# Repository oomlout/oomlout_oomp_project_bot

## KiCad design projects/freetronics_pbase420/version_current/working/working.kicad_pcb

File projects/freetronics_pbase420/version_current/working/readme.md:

# PBASE420 by freetronics  
This is a harvested standardized copy of a project from github.  
The original project can be found at:  
https://github.com/freetronics/PBASE420  
Please consult that link for additional, details, files, and license information.  
Note: It was auto harvested and if the original repo had more than one board file or anything out of the ordinary the files here are likely not representative.

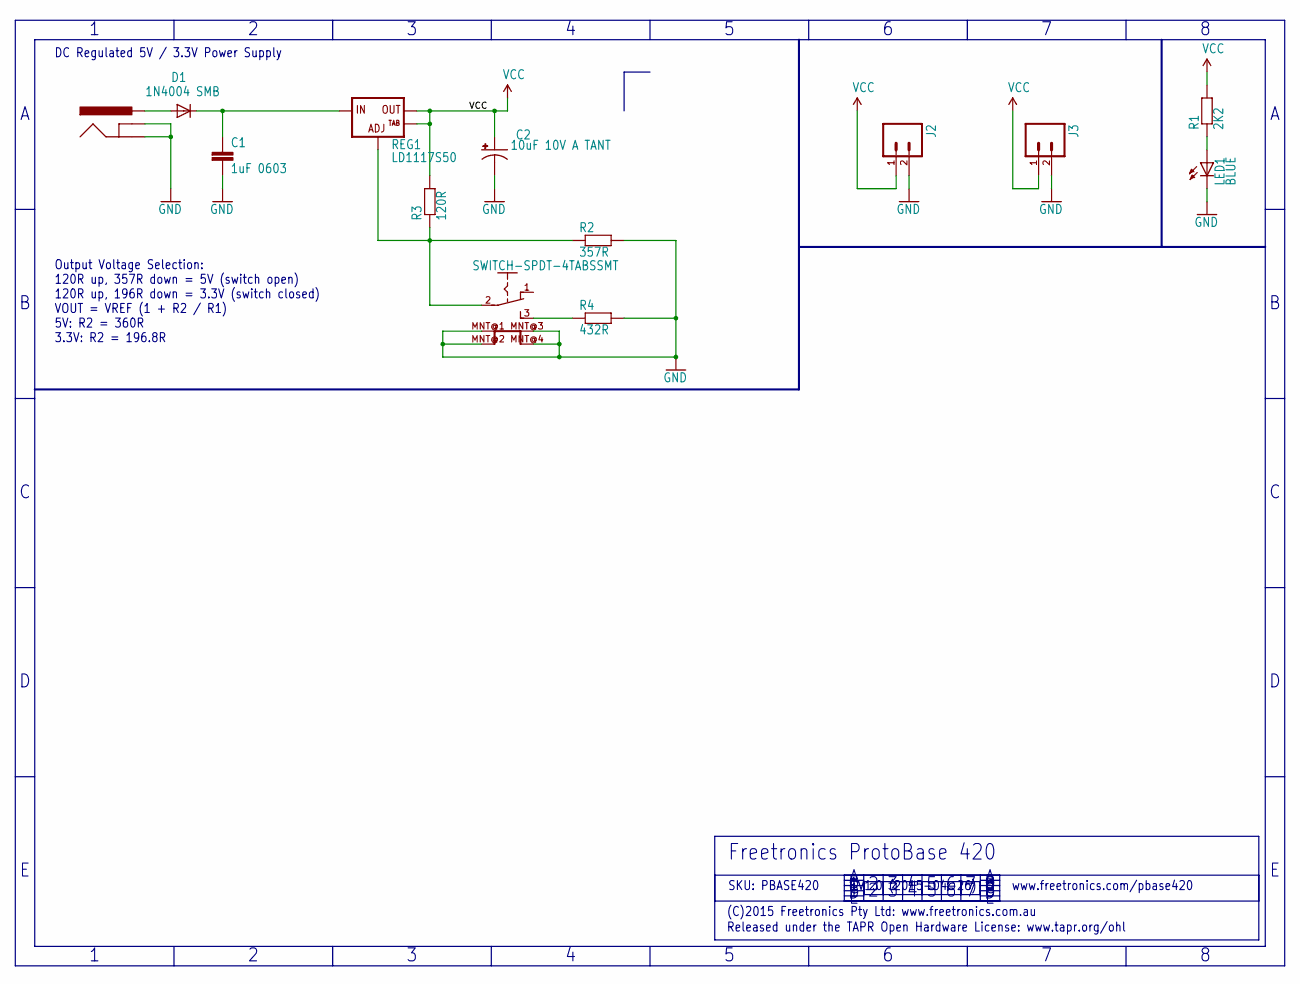
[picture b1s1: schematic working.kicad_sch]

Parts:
C1: 1uF 0603; 0603
C2: 10uF 10V A TANT; EIA3216
D1: 1N4004 SMB; SMB-DIODE
J2, J3: M02PTH; 1X02
J4: POWER_JACKPTH_SLOTS; POWER_JACK_PTH_SLOTS
LED1: BLUE; LED-0603
R1: 2K2; 0603
R2: 357R; 0603
R3: 120R; 0603
R4: 432R; 0603
REG1: LD1117S50; SOT223
SW1: SWITCH-SPDT-4TABSSMT; MK-12C02

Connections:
GND: C1.2, C2.C (-), J2.2, J3.2, J4.GND, J4.GNDBREAK, LED1.C, R2.2, R4.2, SW1.MNT@1, SW1.MNT@2, SW1.MNT@3, SW1.MNT@4
unnamed: LED1.A, R1.1
unnamed: R2.1, R3.1, REG1.1 (ADJ), SW1.2 (COM)
unnamed: R4.1, SW1.3 (B)
unnamed: D1.A, J4.PWR
VCC: C2.A (+), J2.1, J3.1, R1.2, R3.2, REG1.2 (OUT), REG1.4 (OUT@1)
VIN: C1.1, D1.C, REG1.3 (IN)

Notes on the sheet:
SKU: PBASE420
Output Voltage Selection: 120R up, 357R down = 5V (switch open) 120R up, 196R down = 3.3V (switch closed) VOUT = VREF (1 + R2 / R1) 5V: R2 = 360R 3.3V: R2 = 196.8R
www.freetronics.com/pbase420
Released under the TAPR Open Hardware License: www.tapr.org/ohl
DC Regulated 5V / 3.3V Power Supply
(C)2015 Freetronics Pty Ltd: www.freetronics.com.au
V1.0 (2015-04-26)
Freetronics ProtoBase 420

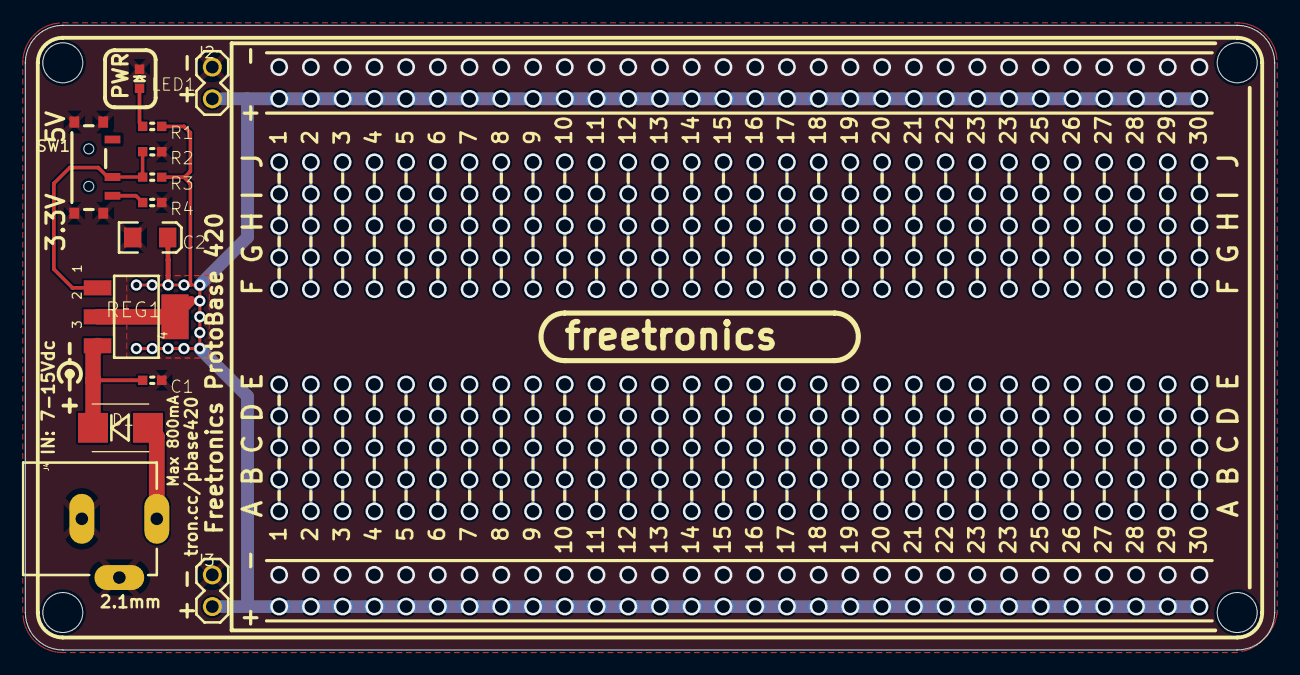
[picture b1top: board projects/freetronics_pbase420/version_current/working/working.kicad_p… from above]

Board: 2 copper layers, 100.0 x 50.0 mm, 17 parts (0 on the bottom side), 7 nets.

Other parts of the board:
@HOLE0, @HOLE1, @HOLE2, @HOLE3: (no value)

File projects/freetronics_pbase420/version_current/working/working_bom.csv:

"Id";"Designator";"Footprint";"Quantity";"Designation";"Supplier and ref";
1;"@HOLE3,@HOLE0,@HOLE2,@HOLE1";"";4;"";;;
2;"J2,J3";"1X02";2;"";;;
3;"R1";"0603";1;"2K2";;;
4;"R2";"0603";1;"357R";;;
5;"SW1";"MK-12C02";1;"MK-12C02-PB";;;
6;"R3";"0603";1;"120R";;;
7;"LED1";"LED-0603";1;"BLUE";;;
8;"D1";"SMB-DIODE";1;"1N4004 SMB";;;
9;"R4";"0603";1;"432R";;;
10;"REG1";"SOT223";1;"LD1117S50";;;
11;"C2";"EIA3216";1;"10uF 10V A TANT";;;
12;"C1";"0603";1;"1uF 0603";;;
13;"J4";"POWER_JACK_PTH_SLOTS";1;"POWER_JACKPTH_SLOTS";;;

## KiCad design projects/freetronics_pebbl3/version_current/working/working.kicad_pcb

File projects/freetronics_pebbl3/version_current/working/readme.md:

# PEBBL3 by freetronics  
This is a harvested standardized copy of a project from github.  
The original project can be found at:  
https://github.com/freetronics/PEBBL3  
Please consult that link for additional, details, files, and license information.  
Note: It was auto harvested and if the original repo had more than one board file or anything out of the ordinary the files here are likely not representative.

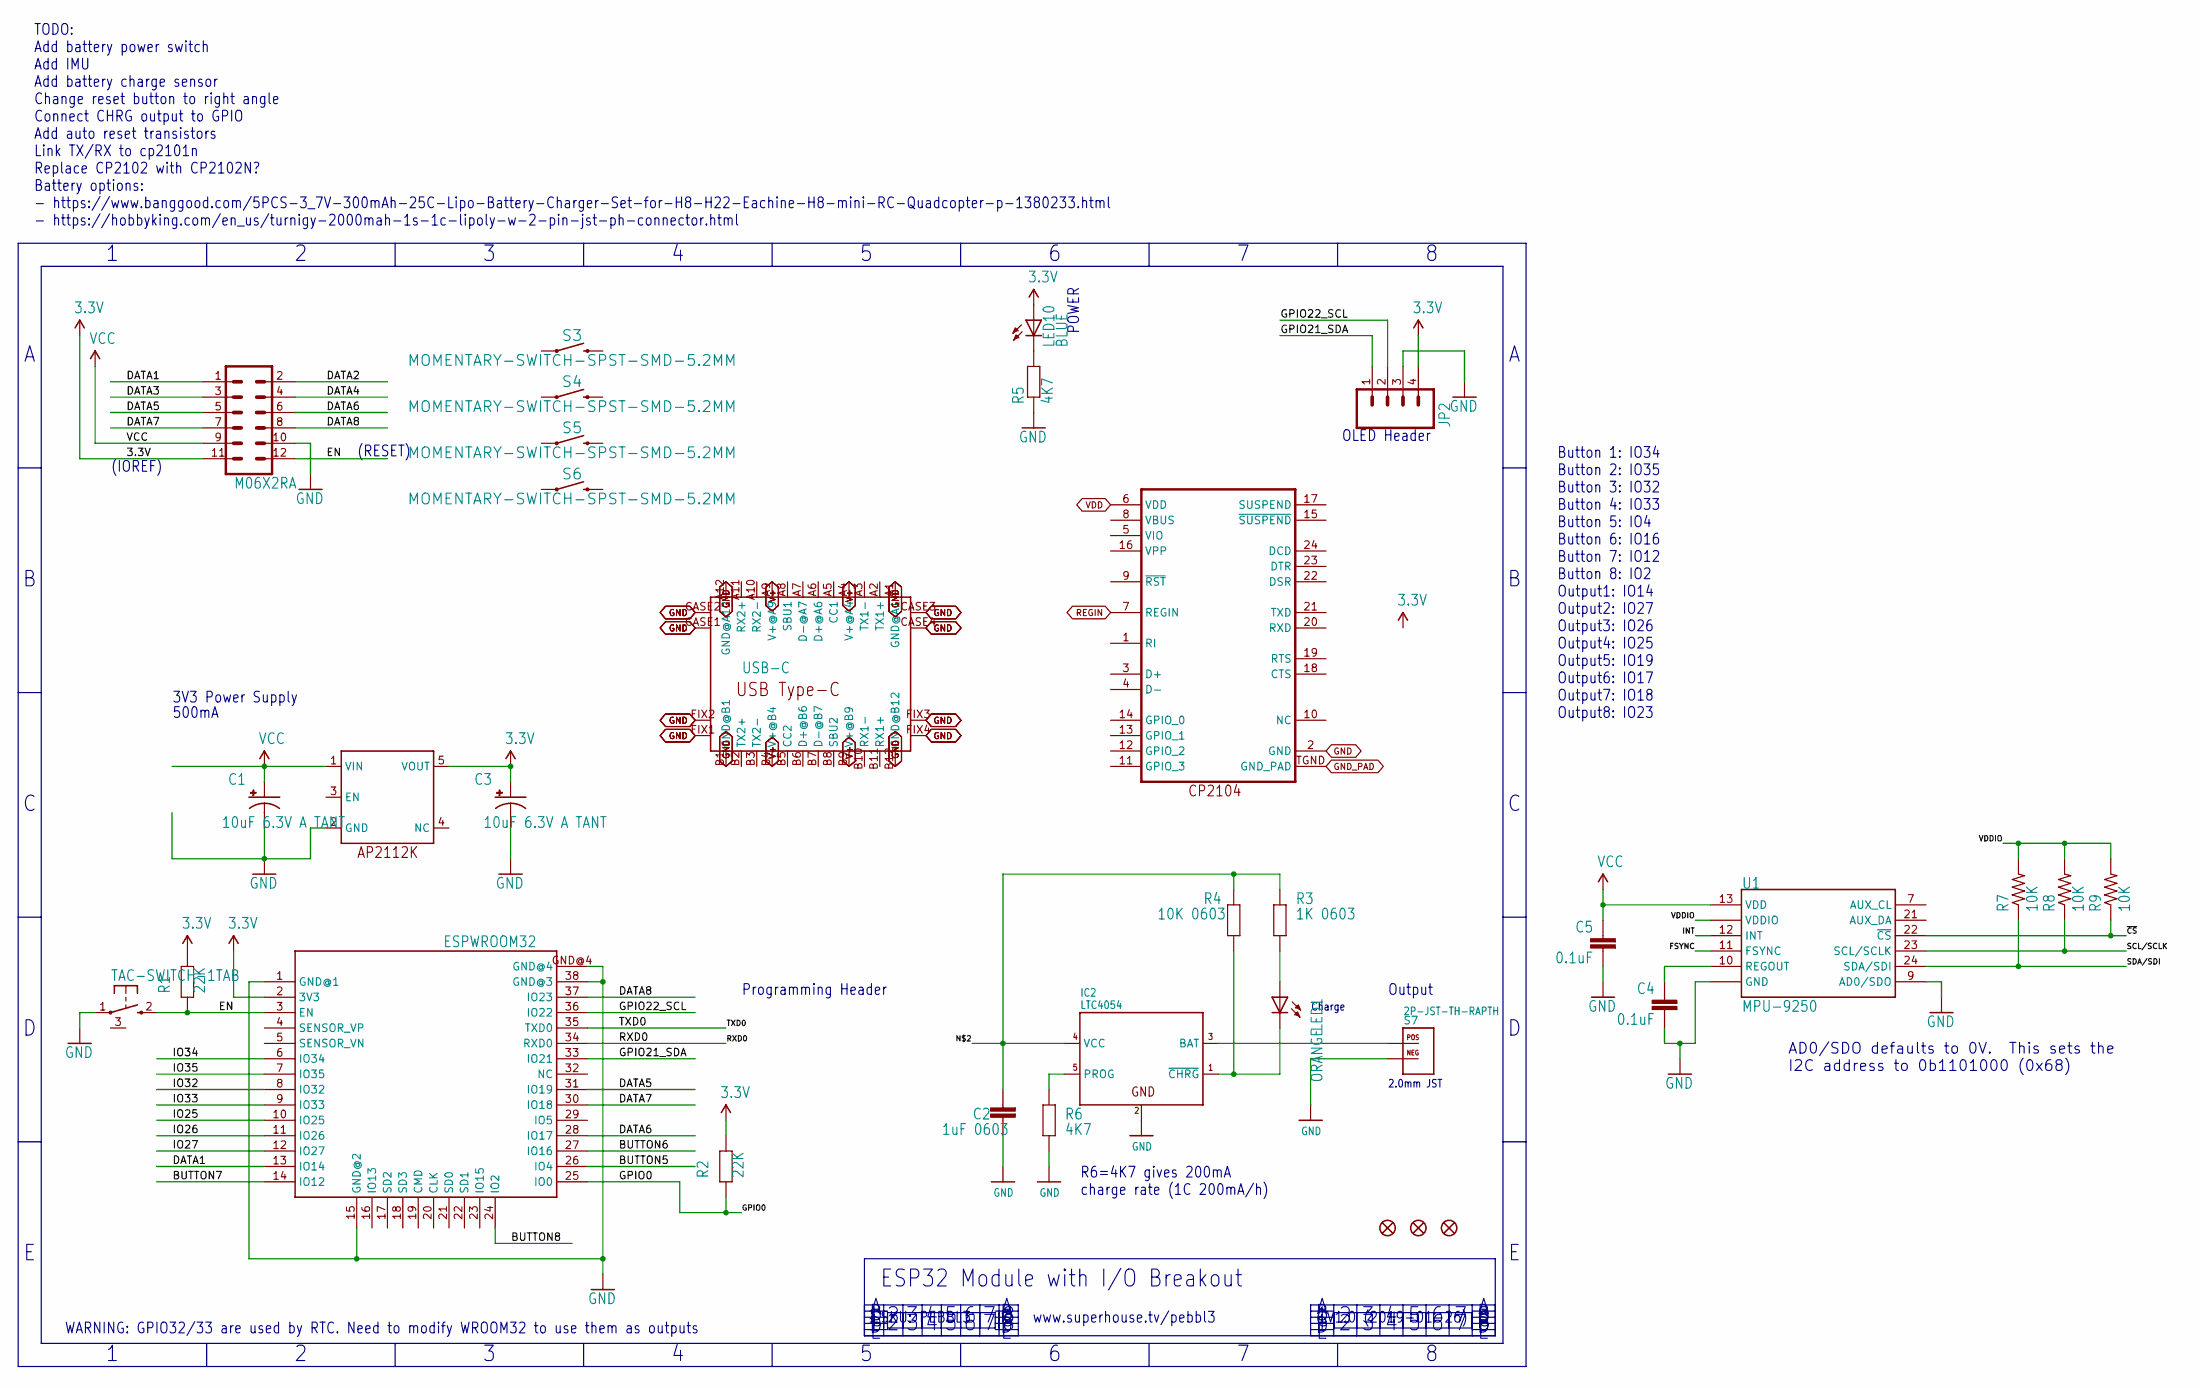
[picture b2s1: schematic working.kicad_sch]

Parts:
C1, C3: 10uF 6.3V A TANT; EIA3216
C2: 1uF 0603; 0603
C4, C5: 0.1uF; 0603-CAP
FID1, FID2, FID3: FIDUCIAL1X2.5; FIDUCIAL-1X2.5
IC1: ESPWROOM32
IC2: LTC4054; SOT23-5
JP2: M04PTH; 1X04
LED1: ORANGE; LED-0603
LED10: BLUE; LED-0603
R1, R2: 22K; 0603
R3: 1K 0603; 0603
R4: 10K 0603; 0603
R5, R6: 4K7; 0603
R7, R8, R9: 10K; 0603-RES
S1: TAC-SWITCH-1TAB; TACT-VERT-1TAB
S3, S4, S5, S6: MOMENTARY-SWITCH-SPST-SMD-5.2MM; TACTILE_SWITCH_SMD_5.2MM
S7: 2P-JST-TH-RAPTH; JST-2MM-TH-RA
U1: MPU-9250; QFN24_PAD
U$1: USB-C; USB-C-U52A
U$2: AP2112KSOT25; SOT23-5
U$3: CP2104; QFN-24
U$6: M06X2RA; 2X6-SHROUDED-RA

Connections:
3.3V: C3.A (+), IC1.2 (3V3), JP2.4, LED10.A, R1.1, R2.1, U$2.5 (VOUT), U$6.11
BUTTON5: IC1.26 (IO4)
BUTTON6: IC1.27 (IO16)
BUTTON7: IC1.14 (IO12)
BUTTON8: IC1.24 (IO2)
DATA1: IC1.13 (IO14), U$6.1
DATA2: U$6.2
DATA3: U$6.3
DATA4: U$6.4
DATA5: IC1.31 (IO19), U$6.5
DATA6: IC1.28 (IO17), U$6.6
DATA7: IC1.30 (IO18), U$6.7
DATA8: IC1.37 (IO23), U$6.8
EN: IC1.3 (EN), R1.2, S1.2, U$6.12
FSYNC: U1.11 (FSYNC)
GND: C1.C (-), C2.1, C3.C (-), C4.2, C5.2, IC1.1 (GND@1), IC1.15 (GND@2), IC1.38 (GND@3), IC1.GND@4, IC2.2 (GND), JP2.3, R5.1, R6.2, S1.1, S7.NEG, U1.9 (AD0/SDO), U1.18 (GND), U1.20 (GND), U1.CENTER (GND), U$1.A1 (GND@A1), U$1.A12 (GND@A12), U$1.B1 (GND@B1), U$1.B12 (GND@B12), U$1.CASE1 (GND@CASE1), U$1.CASE2 (GND@CASE2), U$1.CASE3 (GND@CASE3), U$1.CASE4 (GND@CASE4), U$1.FIX1 (GND@FIX1), U$1.FIX2 (GND@FIX2), U$1.FIX3 (GND@FIX3), U$1.FIX4 (GND@FIX4), U$2.2 (GND), U$3.2 (GND), U$6.10
GND_PAD: U$3.TGND (GND_PAD)
GPIO0: IC1.25 (IO0), R2.2
GPIO21_SDA: IC1.33 (IO21), JP2.1
GPIO22_SCL: IC1.36 (IO22), JP2.2
INT: U1.12 (INT)
IO25: IC1.10 (IO25)
IO26: IC1.11 (IO26)
IO27: IC1.12 (IO27)
IO32: IC1.8 (IO32)
IO33: IC1.9 (IO33)
IO34: IC1.6 (IO34)
IO35: IC1.7 (IO35)
unnamed: C2.2, IC2.4 (VCC), R3.1, R4.1
unnamed: IC2.5 (PROG), R6.1
unnamed: IC2.3 (BAT), S7.POS
unnamed: IC2.1 (~CHRG), LED1.C, R4.2
unnamed: LED1.A, R3.2
unnamed: LED10.C, R5.2
REGIN: U$3.7 (REGIN)
REGOUT: C4.1, U1.10 (REGOUT)
RXD0: IC1.34 (RXD0)
SCL/SCLK: R8.1, U1.23 (SCL/SCLK)
SDA/SDI: R7.1, U1.24 (SDA/SDI)
TXD0: IC1.35 (TXD0)
V+: U$1.A4 (V+@A4), U$1.A9 (V+@A9), U$1.B4 (V+@B4), U$1.B9 (V+@B9)
VDDIO: R7.2, R8.2, R9.2, U1.1 (VDDIO), U1.8 (VDDIO)
~CS: R9.1, U1.22 (~CS)

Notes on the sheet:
Charge
(RESET)
OLED Header
AD0/SDO defaults to 0V. This sets the I2C address to 0b1101000 (0x68)
Output
POWER
2.0mm JST
WARNING: GPIO32/33 are used by RTC. Need to modify WROOM32 to use them as outputs
(IOREF)
Button 1: IO34 Button 2: IO35 Button 3: IO32 Button 4: IO33 Button 5: IO4 Button 6: IO16 Button 7: IO12 Button 8: IO2 Output1: IO14 Output2: IO27 Output3: IO26 Output4: IO25 Output5: IO19 Output6: IO17 Output7: IO18 Output8: IO23
3V3 Power Supply
TODO: Add battery power switch Add IMU Add battery charge sensor Change reset button to right angle Connect CHRG output to GPIO Add auto reset transistors Link TX/RX to cp2101n Replace CP2102 with CP2102N? Battery options: - https://www.banggood.com/5PCS-3_7V-300mAh-25C-Lipo-Battery-Charger-Set-for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
ESP32 Module with I/O Breakout
SKU: PEBBL3
R6=4K7 gives 200mA charge rate (1C 200mA/h)
500mA
V1.0 (2019-01-26)
www.superhouse.tv/pebbl3
Programming Header

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
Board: 2 copper layers, 33 parts (5 on the bottom side), 25 nets, no tracks yet.

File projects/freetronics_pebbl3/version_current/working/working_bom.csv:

"Id";"Designator";"Footprint";"Quantity";"Designation";"Supplier and ref";
1;"S6,S3,S5,S4";"TACTILE_SWITCH_SMD_5.2MM";4;"MOMENTARY-SWITCH-SPST-SMD-5.2MM";;;
2;"R5,R6";"0603";2;"4K7";;;
3;"R1,R2";"0603";2;"22K";;;
4;"R9,R7,R8";"0603-RES";3;"10K";;;
5;"LED10";"LED-0603";1;"BLUE";;;
6;"C4,C5";"0603-CAP";2;"0.1uF";;;
7;"U$3";"QFN-24";1;"CP2104";;;
8;"C3,C1";"EIA3216";2;"10uF 6.3V A TANT";;;
9;"FID3,FID1,FID2";"FIDUCIAL-1X2.5";3;"FIDUCIAL1X2.5";;;
10;"U$2";"SOT23-5";1;"AP2112KSOT25";;;
11;"R3";"0603";1;"1K 0603";;;
12;"U1";"QFN24_PAD";1;"MPU-9250";;;
13;"R4";"0603";1;"10K 0603";;;
14;"LED1";"LED-0603";1;"ORANGE";;;
15;"C2";"0603";1;"1uF 0603";;;
16;"IC2";"SOT23-5";1;"LTC4054";;;
17;"JP2";"1X04";1;"";;;
18;"U$1";"USB-C-U52A";1;"USB-C";;;
19;"S7";"JST-2MM-TH-RA";1;"2P-JST-PTH";;;
20;"S1";"TACT-VERT-1TAB";1;"RESET";;;
21;"U$6";"2X6-SHROUDED-RA";1;"M06X2RA";;;
22;"IC1";"ESPWROOM32";1;"ESPWROOM32";;;

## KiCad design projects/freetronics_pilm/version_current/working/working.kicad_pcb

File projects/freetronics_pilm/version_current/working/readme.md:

# PILM by freetronics  
This is a harvested standardized copy of a project from github.  
The original project can be found at:  
https://github.com/freetronics/PILM  
Please consult that link for additional, details, files, and license information.  
Note: It was auto harvested and if the original repo had more than one board file or anything out of the ordinary the files here are likely not representative.

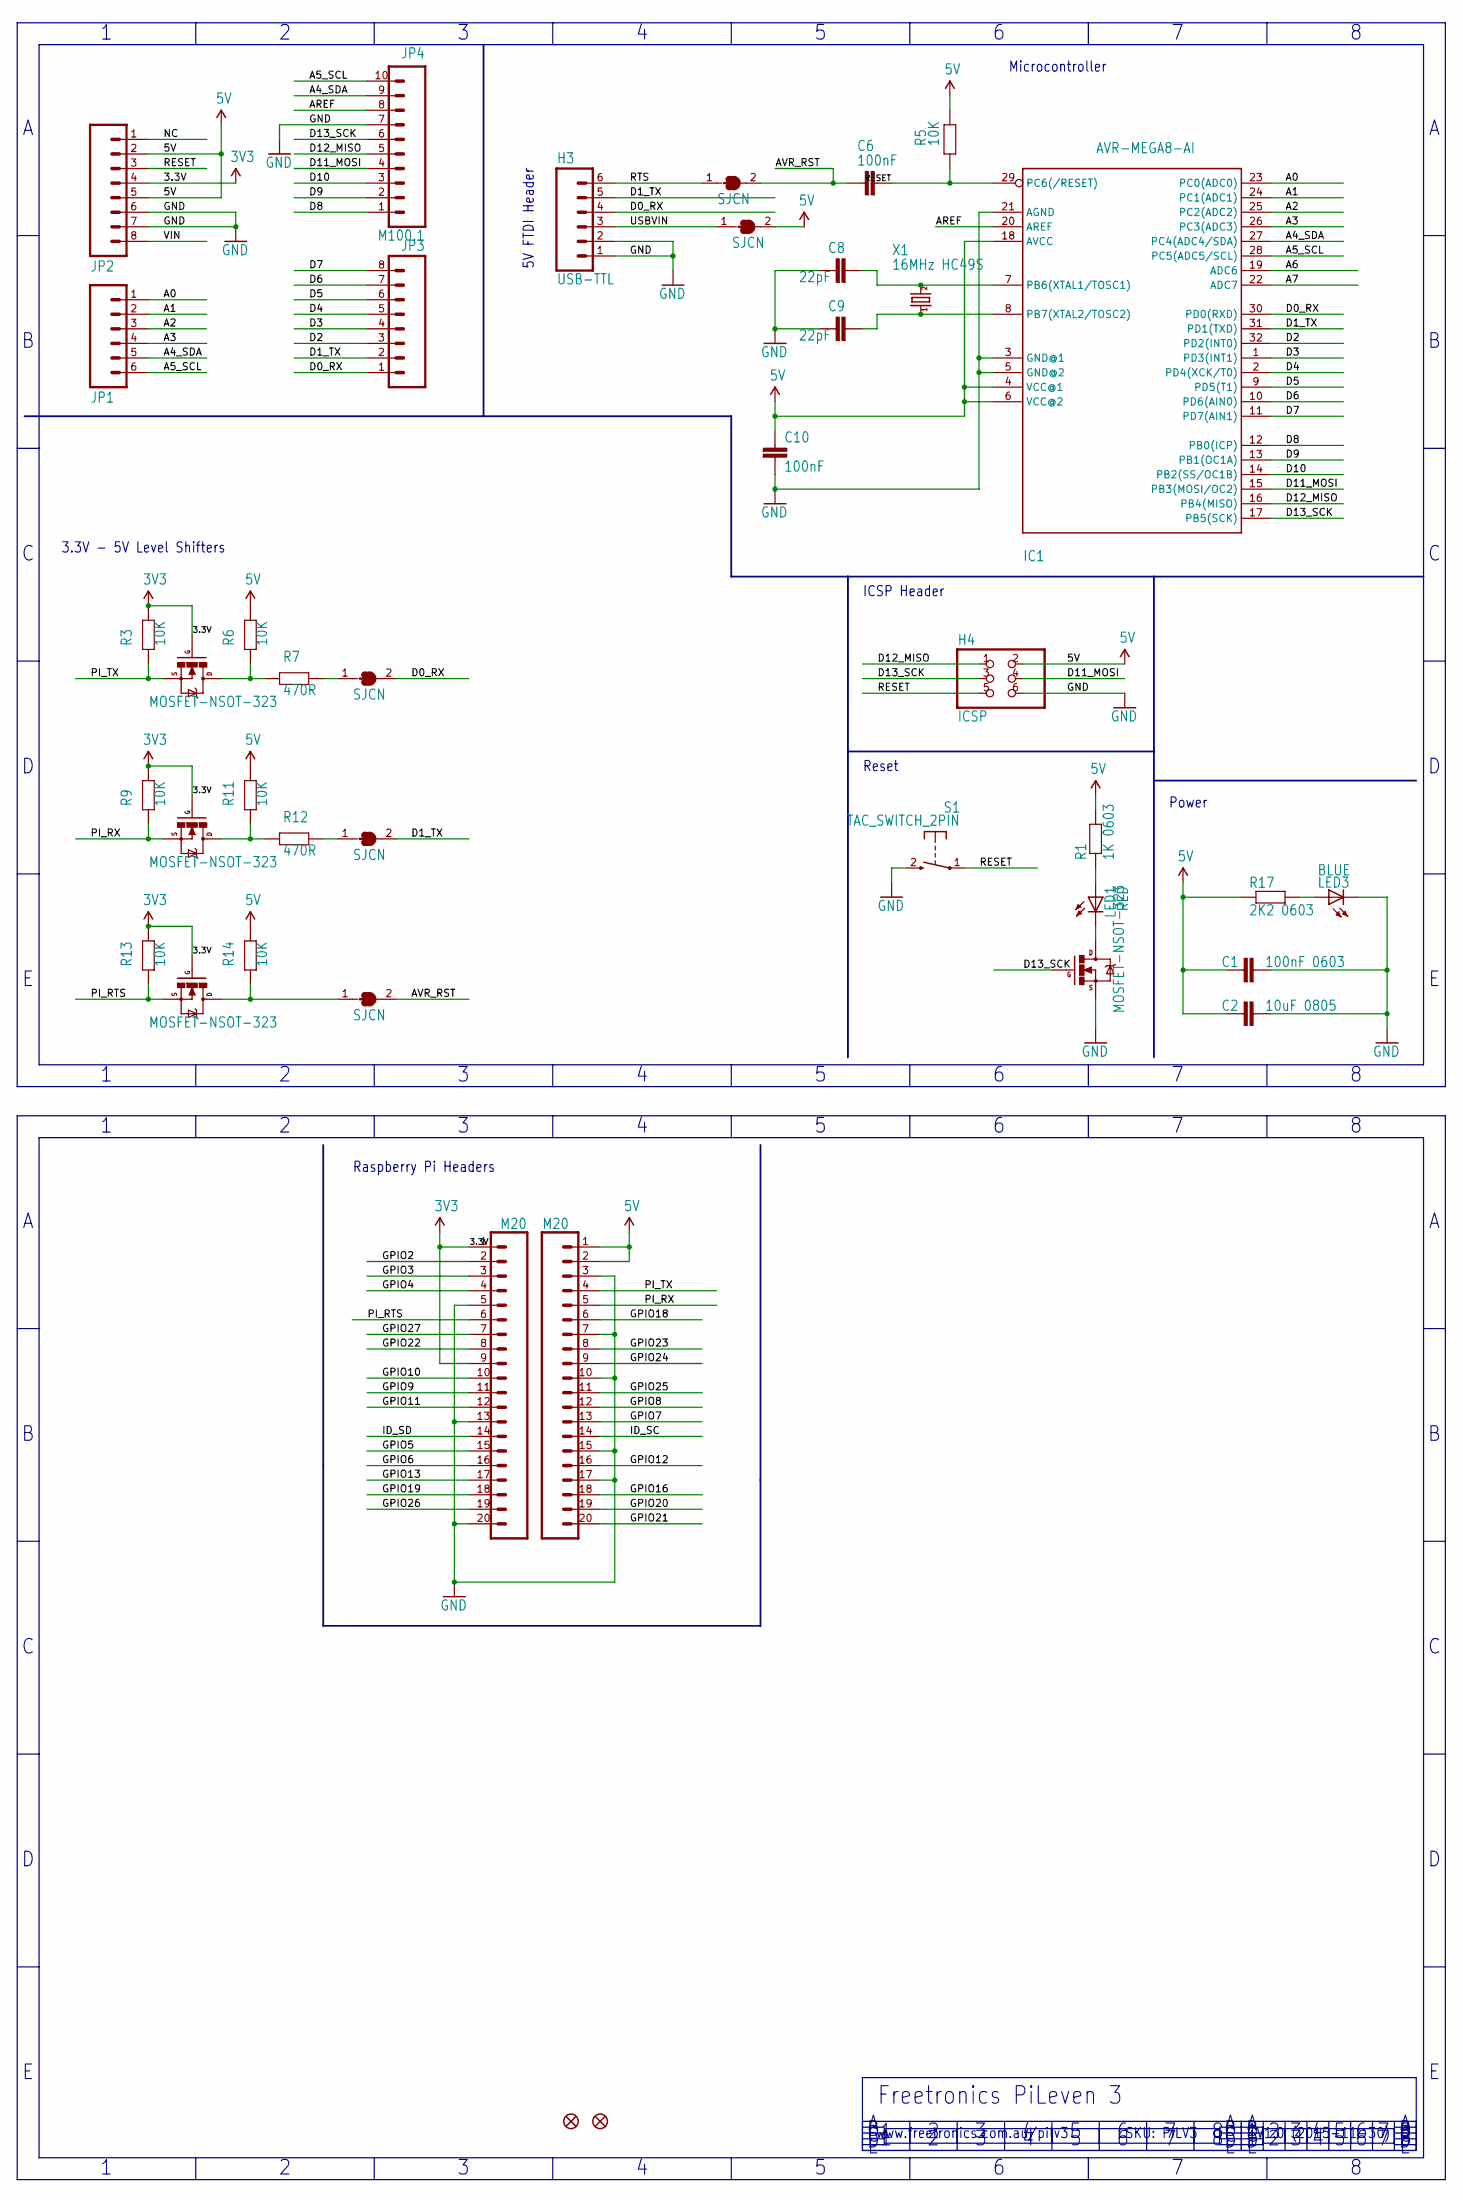
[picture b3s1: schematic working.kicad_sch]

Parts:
C1: 100nF 0603; 0603
C2: 10uF 0805; C0805
C6, C10: 100nF; 0603
C8, C9: 22pF; 0603
H1, H2: M20; 1X20
H3: USB-TTL; 1X06
H4: ICSP; 2X03
IC1: AVR-MEGA8-AI; TQFP32-08
JP1: M06SIP; 1X06
JP2, JP3: M08; 1X08
JP4: M100.1; 1X10
LED1: RED; LED-0603
LED3: BLUE; LED-0603
Q1, Q2, Q3, Q4: MOSFET-NSOT-323; SOT32-3
R1: 1K 0603; 0603
R3, R5, R6, R9, R11, R13, R14: 10K; 0603
R7, R12: 470R; 0603
R17: 2K2 0603; 0603
S1: TAC_SWITCH_2PIN; TACTILE_SWITCH_SMD_2PIN_TINY
SJ1, SJ2, SJ3, SJ4, SJ5: SJCN; SJC
U$4, U$5: FIDUCIAL1X2.5; FIDUCIAL-1X2.5
X1: 16MHz HC49S; HC49U-V

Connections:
3.3V: H1.1, H1.9, JP2.4, Q1.1 (G), Q2.1 (G), Q3.1 (G), R3.1, R9.1, R13.1
5V: C1.1, C2.2, C10.1, H2.1, H2.2, H4.2, IC1.4 (VCC@1), IC1.6 (VCC@2), IC1.18 (AVCC), JP2.2, JP2.5, R1.2, R5.2, R6.1, R11.1, R14.1, R17.1, SJ2.2
A0: IC1.23 (PC0(ADC0)), JP1.1
A1: IC1.24 (PC1(ADC1)), JP1.2
A2: IC1.25 (PC2(ADC2)), JP1.3
A3: IC1.26 (PC3(ADC3)), JP1.4
A4_SDA: IC1.27 (PC4(ADC4/SDA)), JP1.5, JP4.9
A5_SCL: IC1.28 (PC5(ADC5/SCL)), JP1.6, JP4.10
A6: IC1.19 (ADC6)
A7: IC1.22 (ADC7)
AREF: IC1.20 (AREF), JP4.8
AVR_RST: C6.1, SJ1.2, SJ5.2
D0_RX: H3.4, IC1.30 (PD0(RXD)), JP3.1, SJ3.2
D1_TX: H3.5, IC1.31 (PD1(TXD)), JP3.2, SJ4.2
D2: IC1.32 (PD2(INT0)), JP3.3
D3: IC1.1 (PD3(INT1)), JP3.4
D4: IC1.2 (PD4(XCK/T0)), JP3.5
D5: IC1.9 (PD5(T1)), JP3.6
D6: IC1.10 (PD6(AIN0)), JP3.7
D7: IC1.11 (PD7(AIN1)), JP3.8
D8: IC1.12 (PB0(ICP)), JP4.1
D9: IC1.13 (PB1(OC1A)), JP4.2
D10: IC1.14 (PB2(SS/OC1B)), JP4.3
D11_MOSI: H4.4, IC1.15 (PB3(MOSI/OC2)), JP4.4
D12_MISO: H4.1, IC1.16 (PB4(MISO)), JP4.5
D13_SCK: H4.3, IC1.17 (PB5(SCK)), JP4.6, Q4.1 (G)
GND: C1.2, C2.1, C8.1, C9.1, C10.2, H1.5, H1.13, H1.20, H2.3, H2.7, H2.10, H2.15, H2.17, H3.1, H3.2, H4.6, IC1.3 (GND@1), IC1.5 (GND@2), IC1.21 (AGND), JP2.6, JP2.7, JP4.7, LED3.C, Q4.2 (S), S1.2 (S)
GPIO2: H1.2
GPIO3: H1.3
GPIO4: H1.4
GPIO5: H1.15
GPIO6: H1.16
GPIO7: H2.13
GPIO8: H2.12
GPIO9: H1.11
GPIO10: H1.10
GPIO11: H1.12
GPIO12: H2.16
GPIO13: H1.17
GPIO16: H2.18
GPIO18: H2.6
GPIO19: H1.18
GPIO20: H2.19
GPIO21: H2.20
GPIO22: H1.8
GPIO23: H2.8
GPIO24: H2.9
GPIO25: H2.11
GPIO26: H1.19
GPIO27: H1.7
ID_SC: H2.14
ID_SD: H1.14
unnamed: LED3.A, R17.2
unnamed: Q1.3 (D), R6.2, R7.2
unnamed: R7.1, SJ3.1
unnamed: R12.1, SJ4.1
unnamed: C8.2, IC1.7 (PB6(XTAL1/TOSC1)), X1.2
unnamed: Q2.3 (D), R11.2, R12.2
unnamed: Q3.3 (D), R14.2, SJ5.1
unnamed: LED1.C, Q4.3 (D)
unnamed: LED1.A, R1.1
unnamed: C9.2, IC1.8 (PB7(XTAL2/TOSC2)), X1.1
NC: JP2.1
PI_RTS: H1.6, Q3.2 (S), R13.2
PI_RX: H2.5, Q2.2 (S), R9.2
PI_TX: H2.4, Q1.2 (S), R3.2
RESET: C6.2, H4.5, IC1.29 (PC6(/RESET)), JP2.3, R5.1, S1.1
RTS: H3.6, SJ1.1
USBVIN: H3.3, SJ2.1
VIN: JP2.8

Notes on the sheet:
Microcontroller
Freetronics PiLeven 3
Power
www.freetronics.com.au/pilv3
3.3V - 5V Level Shifters
ICSP Header
SKU: PILV3
5V FTDI Header
V1.0 (2015-11-30)
Reset
Raspberry Pi Headers

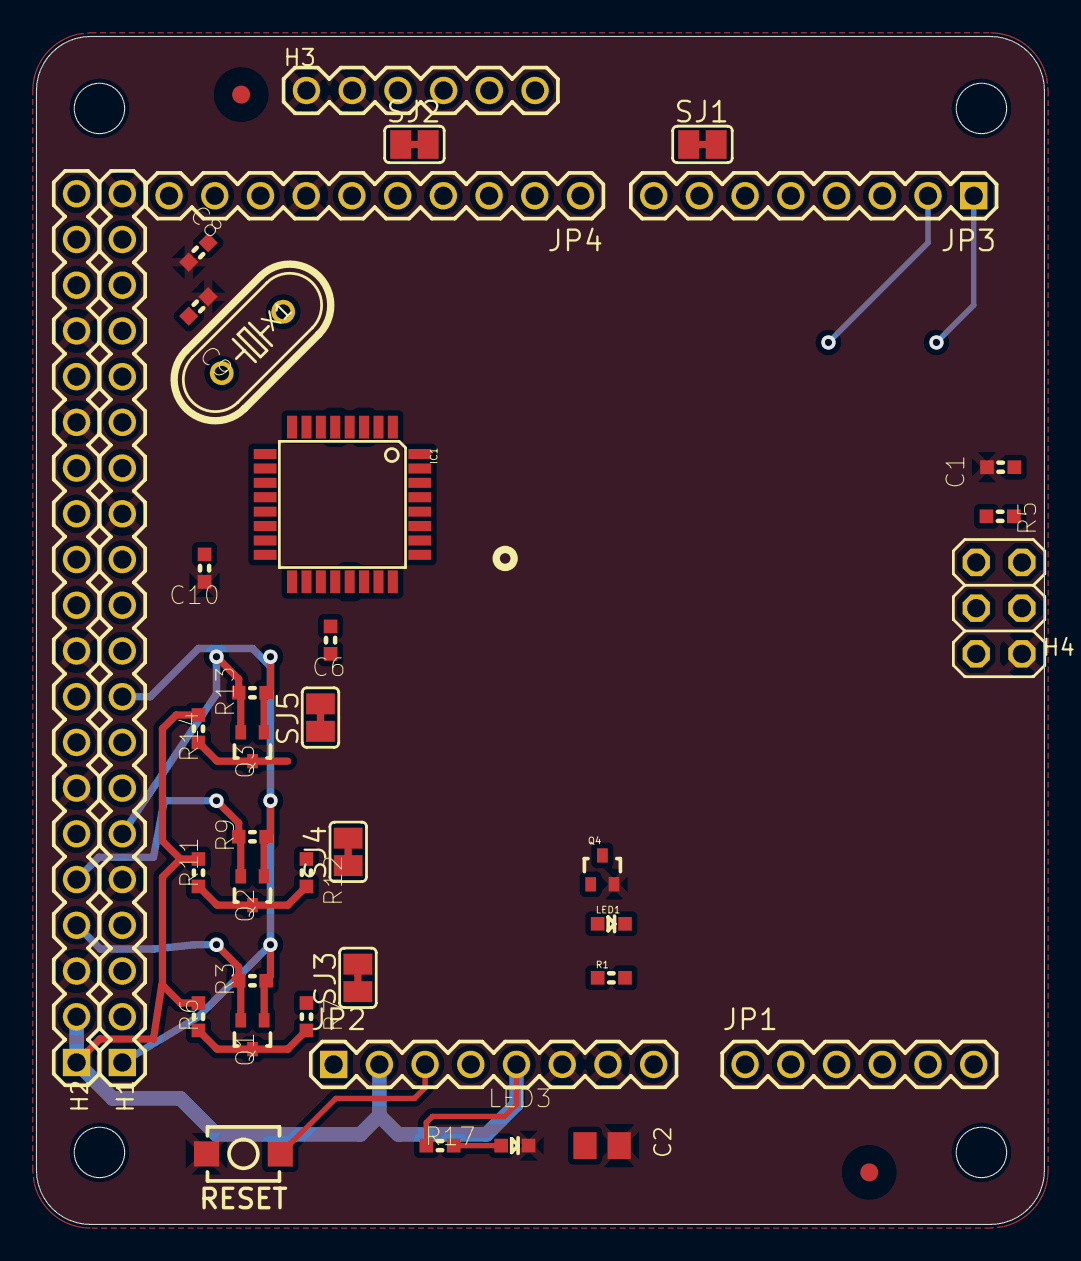
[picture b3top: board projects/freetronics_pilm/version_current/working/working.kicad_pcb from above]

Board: 2 copper layers, 56.0 x 66.0 mm, 45 parts (0 on the bottom side), 41 nets.

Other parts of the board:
@HOLE0, @HOLE1, @HOLE2, @HOLE3: (no value)

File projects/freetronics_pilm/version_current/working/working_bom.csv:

"Id";"Designator";"Footprint";"Quantity";"Designation";"Supplier and ref";
1;"@HOLE0,@HOLE3,@HOLE1,@HOLE2";"";4;"";;;
2;"SJ5,SJ4,SJ1,SJ2,SJ3";"SJC";5;"SJCN";;;
3;"U$4,U$5";"FIDUCIAL-1X2.5";2;"FIDUCIAL1X2.5";;;
4;"R3,R5,R14,R9,R11,R6,R13";"0603";7;"10K";;;
5;"JP1";"1X06";1;"";;;
6;"C8,C9";"0603";2;"22pF";;;
7;"H4";"2X03";1;"ICSP";;;
8;"C1";"0603";1;"100nF 0603";;;
9;"JP3,JP2";"1X08";2;"";;;
10;"Q3,Q4,Q1,Q2";"SOT32-3";4;"RJU003N03 N-MOSFET";;;
11;"C2";"C0805";1;"10uF 0805";;;
12;"LED1";"LED-0603";1;"RED";;;
13;"R12,R7";"0603";2;"470R";;;
14;"LED3";"LED-0603";1;"BLUE";;;
15;"C6,C10";"0603";2;"100nF";;;
16;"IC1";"TQFP32-08";1;"ATMEGA328P";;;
17;"JP4";"1X10";1;"M100.1";;;
18;"H2,H1";"1X20";2;"M20";;;
19;"X1";"HC49U-V";1;"16MHz HC49S";;;
20;"R1";"0603";1;"1K 0603";;;
21;"S1";"TACTILE_SWITCH_SMD_2PIN_TINY";1;"RESET";;;
22;"R17";"0603";1;"2K2 0603";;;
23;"H3";"1X06";1;"USB-TTL";;;

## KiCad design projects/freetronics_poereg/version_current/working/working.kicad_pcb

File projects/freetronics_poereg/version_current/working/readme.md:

# POEREG by freetronics  
This is a harvested standardized copy of a project from github.  
The original project can be found at:  
https://github.com/freetronics/POEREG  
Please consult that link for additional, details, files, and license information.  
Note: It was auto harvested and if the original repo had more than one board file or anything out of the ordinary the files here are likely not representative.

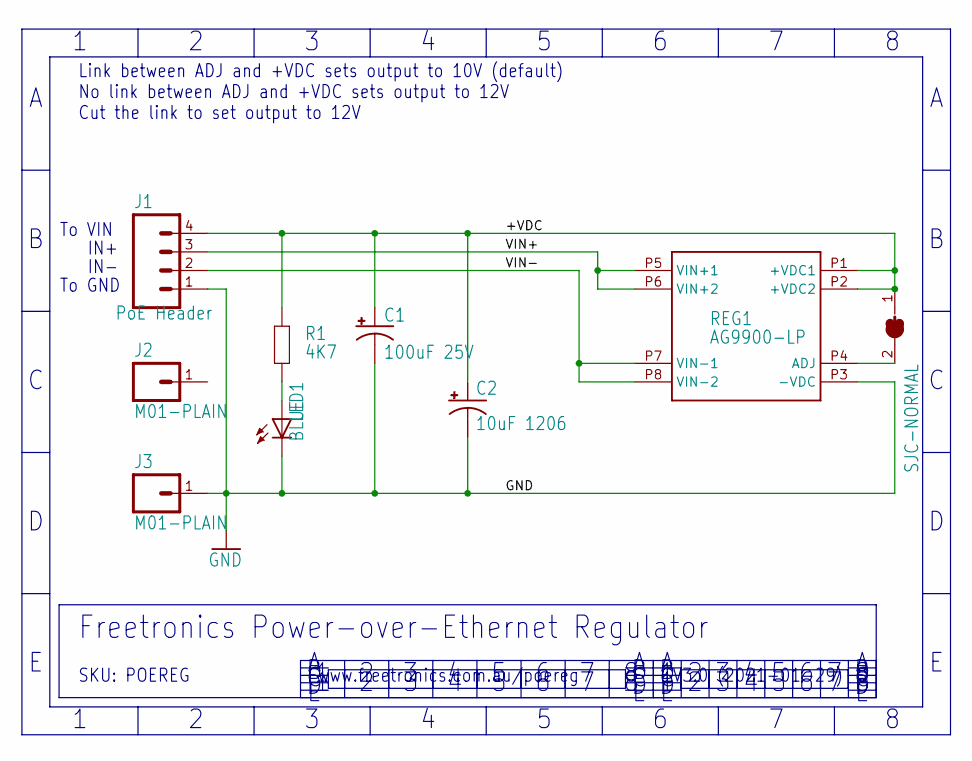
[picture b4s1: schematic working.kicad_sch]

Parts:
C1: 100uF 25V; PANASONIC_D
C2: 10uF 1206; EIA3216
J1: PoE Header; 1X04
J2, J3: M01-PLAIN; 1X01
LED1: BLUE; LED-0603
R1: 4K7; R0603
REG1: AG9900-LP; AG9900LP
SJ1: SJC-NORMAL; SJC

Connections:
+VDC: C1.+, C2.A (+), J1.4, R1.1, REG1.P1 (+VDC1), REG1.P2 (+VDC2), SJ1.1
GND: C1.-, C2.C (-), J1.1, J3.1, LED1.C, REG1.P3 (-VDC)
unnamed: REG1.P4 (ADJ), SJ1.2
unnamed: LED1.A, R1.2
VIN+: J1.3, REG1.P5 (VIN+1), REG1.P6 (VIN+2)
VIN-: J1.2, REG1.P7 (VIN-1), REG1.P8 (VIN-2)

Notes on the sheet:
To VIN
V3.0 (2021-01-29)
To GND
Freetronics Power-over-Ethernet Regulator
SKU: POEREG
www.freetronics.com.au/poereg
IN+
IN-
Link between ADJ and +VDC sets output to 10V (default) No link between ADJ and +VDC sets output to 12V Cut the link to set output to 12V

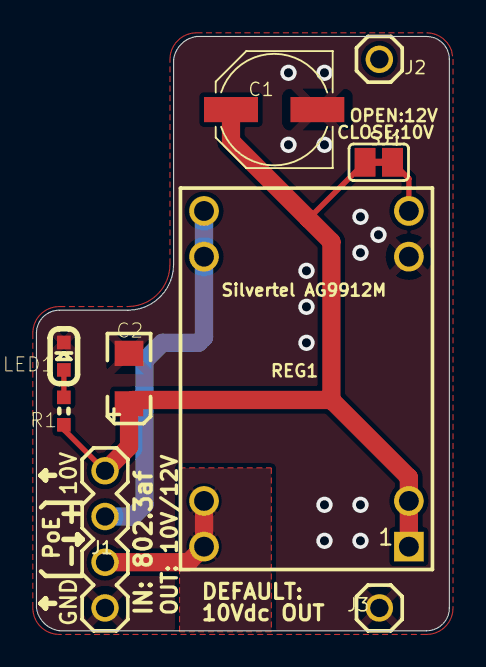
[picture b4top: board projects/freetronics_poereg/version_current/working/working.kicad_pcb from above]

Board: 2 copper layers, 22.9 x 33.0 mm, 9 parts (0 on the bottom side), 6 nets.

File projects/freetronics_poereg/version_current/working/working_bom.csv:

"Id";"Designator";"Footprint";"Quantity";"Designation";"Supplier and ref";
1;"C1";"PANASONIC_D";1;"100uF 25V";;;
2;"J3,J2";"1X01";2;"M01-PLAIN";;;
3;"LED1";"LED-0603";1;"BLUE";;;
4;"REG1";"AG9900LP";1;"AG9912LP";;;
5;"SJ1";"SJC";1;"SJC-NORMAL";;;
6;"J1";"1X04";1;"PoE Header";;;
7;"R1";"R0603";1;"4K7";;;
8;"C2";"EIA3216";1;"10uF 1206";;;

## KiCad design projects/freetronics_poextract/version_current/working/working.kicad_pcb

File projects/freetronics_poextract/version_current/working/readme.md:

# POEXTRACT by freetronics  
This is a harvested standardized copy of a project from github.  
The original project can be found at:  
https://github.com/freetronics/POEXTRACT  
Please consult that link for additional, details, files, and license information.  
Note: It was auto harvested and if the original repo had more than one board file or anything out of the ordinary the files here are likely not representative.

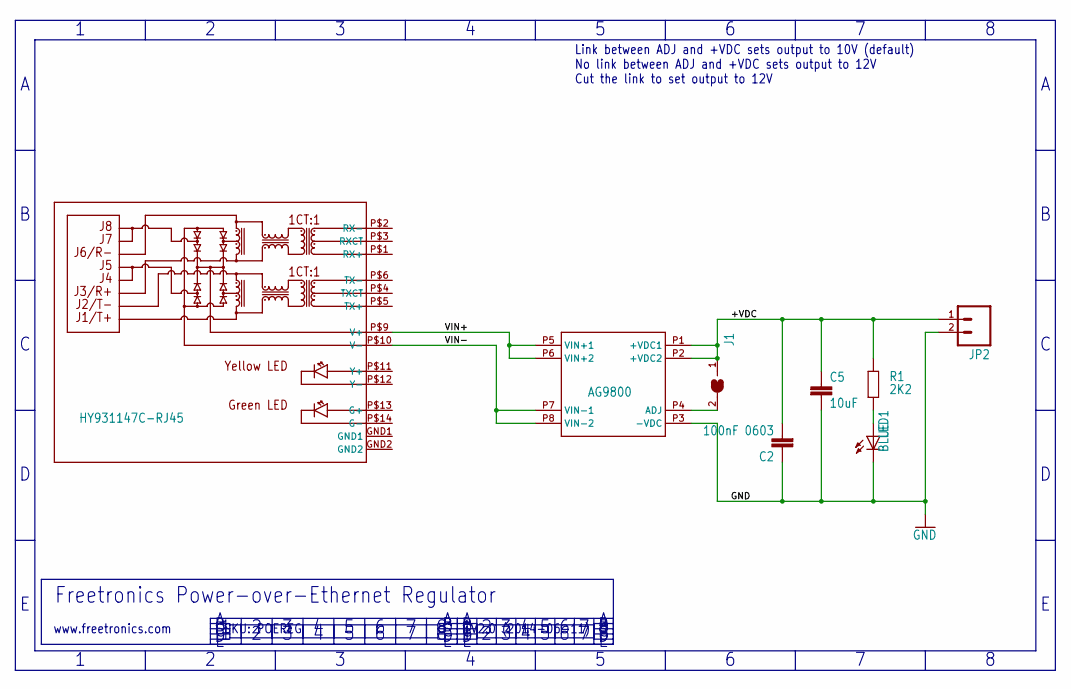
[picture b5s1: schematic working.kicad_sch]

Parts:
C2: 100nF 0603; 0603
C5: 10uF; C1206
J1: SJN; SJ
JP2: M025MM; SCREWTERMINAL-5MM-2
LED1: BLUE; LED-0603
R1: 2K2; 0603
REG1: AG9800
U$1: HY931147C-RJ45; HY931147C

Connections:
+VDC: C2.2, C5.1, J1.1, JP2.1, R1.1, REG1.P1 (+VDC1), REG1.P2 (+VDC2)
GND: C2.1, C5.2, JP2.2, LED1.C, REG1.P3 (-VDC)
unnamed: J1.2, REG1.P4 (ADJ)
unnamed: LED1.A, R1.2
VIN+: REG1.P5 (VIN+1), REG1.P6 (VIN+2), U$1.P$9 (V+)
VIN-: REG1.P7 (VIN-1), REG1.P8 (VIN-2), U$1.P$10 (V-)

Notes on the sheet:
Link between ADJ and +VDC sets output to 10V (default) No link between ADJ and +VDC sets output to 12V Cut the link to set output to 12V
SKU: POEREG
V2.0 (2014-06-11)
Freetronics Power-over-Ethernet Regulator
www.freetronics.com

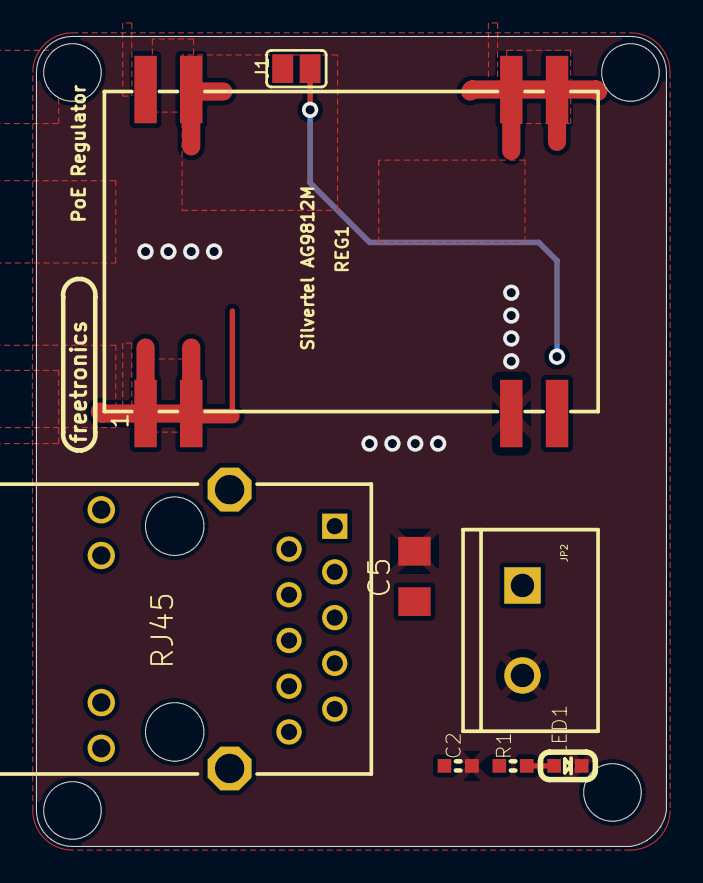
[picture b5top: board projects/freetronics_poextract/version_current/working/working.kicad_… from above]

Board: 2 copper layers, 35.0 x 45.0 mm, 12 parts (0 on the bottom side), 6 nets.

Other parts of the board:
@HOLE0, @HOLE1, @HOLE2, @HOLE3: (no value)

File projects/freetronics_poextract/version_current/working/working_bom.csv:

"Id";"Designator";"Footprint";"Quantity";"Designation";"Supplier and ref";
1;"@HOLE2,@HOLE0,@HOLE1,@HOLE3";"";4;"";;;
2;"U$1";"HY931147C";1;"HY931147C-RJ45";;;
3;"J1";"SJ";1;"";;;
4;"LED1";"LED-0603";1;"BLUE";;;
5;"REG1";"AG9800";1;"AG9800";;;
6;"R1";"0603";1;"2K2";;;
7;"JP2";"SCREWTERMINAL-5MM-2";1;"";;;
8;"C5";"C1206";1;"10uF";;;
9;"C2";"0603";1;"100nF 0603";;;

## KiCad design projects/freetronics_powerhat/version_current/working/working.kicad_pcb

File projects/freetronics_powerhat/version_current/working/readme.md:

# POWERHAT by freetronics  
This is a harvested standardized copy of a project from github.  
The original project can be found at:  
https://github.com/freetronics/POWERHAT  
Please consult that link for additional, details, files, and license information.  
Note: It was auto harvested and if the original repo had more than one board file or anything out of the ordinary the files here are likely not representative.

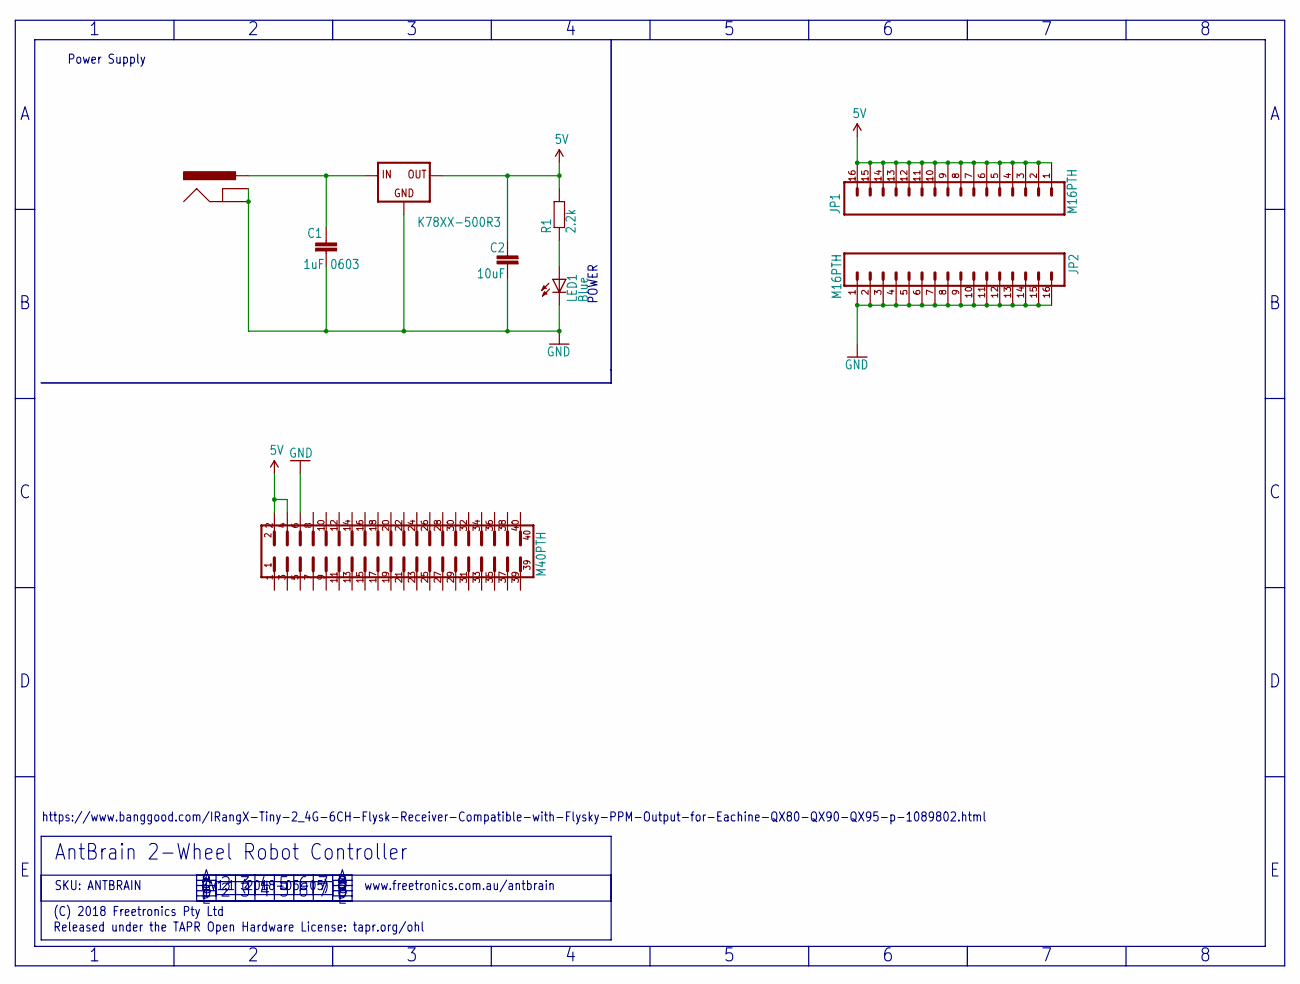
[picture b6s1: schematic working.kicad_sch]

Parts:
C1: 1uF 0603; 0603
C2: 10uF; 0805
J1: POWER_JACKPTH_SLOTS; POWER_JACK_PTH_SLOTS
JP1, JP2: M16PTH; 1X16
LED1: Blue; LED-0603
R1: 2.2k; 0603
REG1: K78XX-500R3
U$2: M40PTH; 2X20

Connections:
5V: C2.1, JP1.1, JP1.2, JP1.3, JP1.4, JP1.5, JP1.6, JP1.7, JP1.8, JP1.9, JP1.10, JP1.11, JP1.12, JP1.13, JP1.14, JP1.15, JP1.16, R1.2, REG1.3 (OUT), U$2.2, U$2.4
GND: C1.2, C2.2, J1.GND, J1.GNDBREAK, JP2.1, JP2.2, JP2.3, JP2.4, JP2.5, JP2.6, JP2.7, JP2.8, JP2.9, JP2.10, JP2.11, JP2.12, JP2.13, JP2.14, JP2.15, JP2.16, LED1.C, REG1.2 (GND), U$2.6
unnamed: LED1.A, R1.1
VBAT: C1.1, J1.PWR, REG1.1 (IN)

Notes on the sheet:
https://www.banggood.com/IRangX-Tiny-2_4G-6CH-Flysk-Receiver-Compatible-with-Flysky-PPM-Output-for-Eachine-QX80-QX90-QX95-p-1089802.html
SKU: ANTBRAIN
Released under the TAPR Open Hardware License: tapr.org/ohl
AntBrain 2-Wheel Robot Controller
www.freetronics.com.au/antbrain
Power Supply
POWER
V1.1 (2018-05-05)
(C) 2018 Freetronics Pty Ltd

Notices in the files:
projects/freetronics_pbase420/version_current/working/working.kicad_pcb:
Copyright 2015 Freetronics Pty Ltd
projects/freetronics_pebbl3/version_current/working/working.kicad_pcb:
(C)2018 SuperHouse Automation P/L
projects/freetronics_pilevenmini/version_current/working/working.kicad_sch:
Licensed under TAPR Open Hardware License
projects/freetronics_pilm/version_current/working/working.kicad_pcb:
(C)2017 Freetronics Pty Ltd
projects/freetronics_poereg/version_current/working/working.kicad_pcb:
(c) 2013-2021 Freetronics Pty Ltd
